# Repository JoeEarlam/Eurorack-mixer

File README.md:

# Eurorack-Mixer
This is a basic, 8 channel mixer for eurorack and compatible modular synthesisers.

It should also work on similar systems, such as +/-15V systems and hifi (with an appropriate bipolar power supply).

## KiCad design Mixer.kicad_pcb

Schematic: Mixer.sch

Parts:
C1, C2, C3, C4, C5, C6, C7, C8, C11, C15, C16: 10u; C_0805_2012Metric_Pad1.15x1.40mm_HandSolder
C9, C10, C13, C14: 100n; C_0805_2012Metric_Pad1.15x1.40mm_HandSolder
J1, J2, J3, J4, J5, J6, J7, J8, J9, J10, J11: JST XH; JST_XH_B02B-XH-A_1x02_P2.50mm_Vertical
J12: Conn_01x03_Female; JST_XH_B03B-XH-A_1x03_P2.50mm_Vertical
L1, L2: LQM21DN220N00L; R_0805_2012Metric_Pad1.15x1.40mm_HandSolder
R1, R2, R3, R4, R5, R6, R7, R8: 5K6; R_0805_2012Metric_Pad1.15x1.40mm_HandSolder
R9, R10, R11: 10K; R_0805_2012Metric_Pad1.15x1.40mm_HandSolder
R12: 2K5; R_0805_2012Metric_Pad1.15x1.40mm_HandSolder
R13: 120R; R_0805_2012Metric_Pad1.15x1.40mm_HandSolder
RV1, RV2, RV3, RV4, RV5, RV6, RV7, RV8: 10KA; BOURNS-PTA4543_45mm-slide-pot
RV9: 10KA; JST_XH_B03B-XH-A_1x03_P2.50mm_Vertical
U1: NE5532; SOIC-8_3.9x4.9mm_P1.27mm

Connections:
+12V: C9.1, C13.2, C15.2, L1.2, U1.8 (V+)
-12V: C10.2, C14.2, C16.2, L2.2, U1.4 (V-)
/MIX_0: R1.1, R2.1, R3.1, R4.1, R5.1, R6.1, R7.1, R8.1, R9.2, U1.2 (-)
GND: C9.2, C10.1, C13.1, C14.1, C15.1, C16.1, J1.1, J2.1, J3.1, J4.1, J5.1, J6.1, J7.1, J8.1, J9.1, J10.1, J11.1, J12.1, R10.1, R12.1, RV1.1, RV2.1, RV3.1, RV4.1, RV5.1, RV6.1, RV7.1, RV8.1, RV9.1, U1.3 (+)
unnamed: C1.1, RV1.3
unnamed: C1.2, J1.2
unnamed: C2.1, RV2.3
unnamed: C2.2, J2.2
unnamed: C3.1, RV3.3
unnamed: C3.2, J3.2
unnamed: C4.1, RV4.3
unnamed: C4.2, J4.2
unnamed: C5.1, RV5.3
unnamed: C5.2, J5.2
unnamed: C6.1, RV6.3
unnamed: C6.2, J6.2
unnamed: C7.1, RV7.3
unnamed: C7.2, J7.2
unnamed: C8.1, RV8.3
unnamed: C8.2, J8.2
unnamed: C11.1, J11.2, R10.2, R11.2, RV9.3
unnamed: C11.2, R9.1, U1.1
unnamed: J9.2, R13.2
unnamed: J10.2, R11.1, R12.2
unnamed: J12.2, L2.1
unnamed: J12.3, L1.1
unnamed: R1.2, RV1.2
unnamed: R2.2, RV2.2
unnamed: R3.2, RV3.2
unnamed: R4.2, RV4.2
unnamed: R5.2, RV5.2
unnamed: R6.2, RV6.2
unnamed: R7.2, RV7.2
unnamed: R8.2, RV8.2
unnamed: R13.1, U1.6 (-), U1.7
unnamed: RV9.2, U1.5 (+)

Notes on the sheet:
Line level
Eurorack level
Headphones

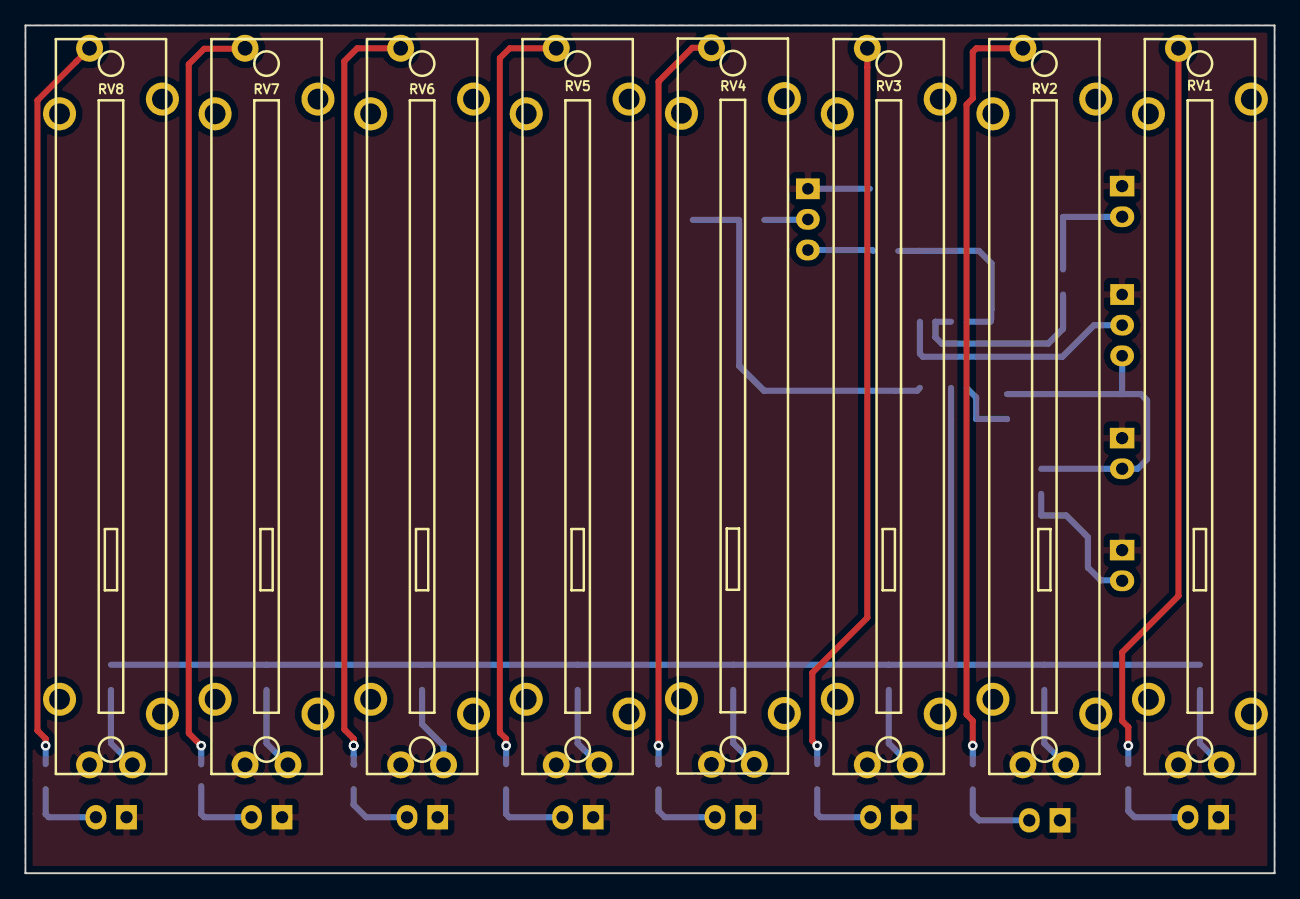
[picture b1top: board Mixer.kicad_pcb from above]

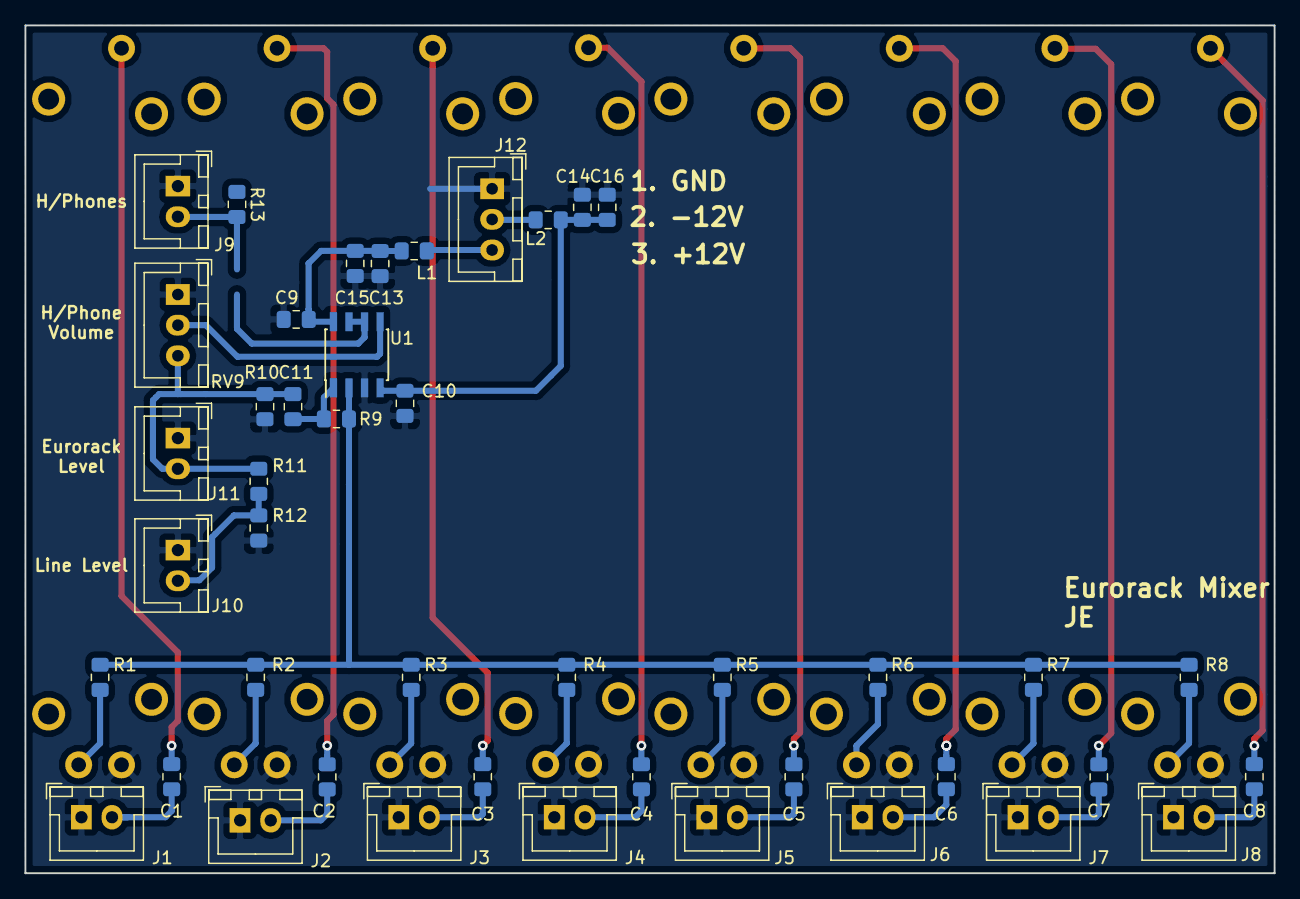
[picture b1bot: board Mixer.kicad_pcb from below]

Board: 2 copper layers, 102.0 x 69.2 mm, 52 parts (44 on the bottom side), 36 nets.

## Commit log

2018-11-15 add pdf schematic
2019-01-10 bugfix after prototype build
2019-01-24 added git ignore
